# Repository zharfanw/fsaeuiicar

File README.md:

# UIIs Formula Students Car 2018
Repo ini merupakan dokumentasi dari mobil listrik UII 2018.
## Dokumentasi Link
Full PDF Dokumentasi [klik dsini](https://github.com/zharfanw/fsaeuiicar/blob/master/Dokumentasi/Dokumentasi%20Elektrik%20Mobil%20SFJ2018%20UII_v2.pdf "Dokumentasi Elektrik Mobil SFJ2018 UII_v2.pdf")
## Kontributor Dokumentasi

 - Muhammad Zharfan Wiranata
 - Muh Fanriado
 - Kristamayu
 - Rudi Arta
 - Akhid Sulthoni
 - Fauzi HPM
 - Muh Dzulfiqar
 - Refhan Naparin
 - Hilal Pambudi
 - Faiz Isbat
 - Muh Iqbal
 - Jabar Lazuarde

<!--stackedit_data:
eyJoaXN0b3J5IjpbLTQxOTc5MTk5MiwxOTc0MTc4MTIxLDU1Nz
E1NDAyNl19
-->

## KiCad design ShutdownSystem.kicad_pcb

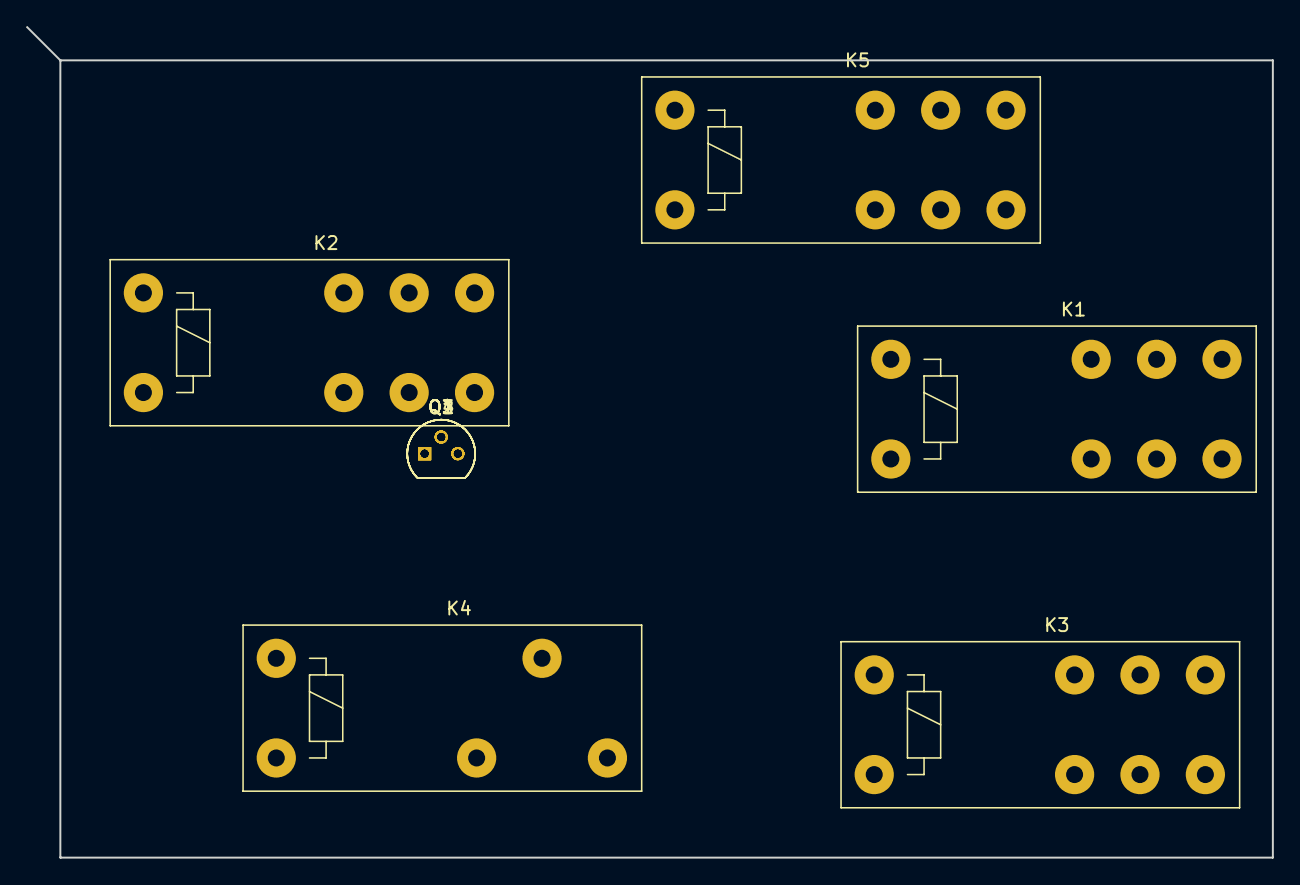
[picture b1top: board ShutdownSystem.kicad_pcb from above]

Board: 2 copper layers, 95.3 x 63.5 mm, 9 parts (0 on the bottom side), 10 nets, no tracks yet.

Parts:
K1, K2, K3, K5: FINDER-41.52; Relay_DPDT_Finder_40.52
K4: FINDER-40.51; Relay_SPDT_Finder_40.51
Q1, Q2, Q4: MPSA92; TO-92_Molded_Narrow
Q3: MPSA42; TO-92_Molded_Narrow

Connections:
+VDC: K1.21, K4.11, Q1.1, Q2.1, Q4.1
GND: K1.A2, K2.A2, K3.A2, K4.A1, K5.A1
unnamed: K1.11, K1.A1, Q1.3
unnamed: K2.11, K2.A1, Q2.3
unnamed: K3.11, K3.A1, Q3.1, Q4.3
unnamed: K1.12, K2.12, K3.12
unnamed: K1.22, K2.21
unnamed: K2.22, K3.21
unnamed: K4.A2, K5.11, K5.21, K5.A2
unnamed: Q3.3, Q4.2

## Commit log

2019-09-29 Menambahkan Dokumentasi mobil sementara
2019-11-20 New Update
2019-11-20 README.md updated from https://stackedit.io/
